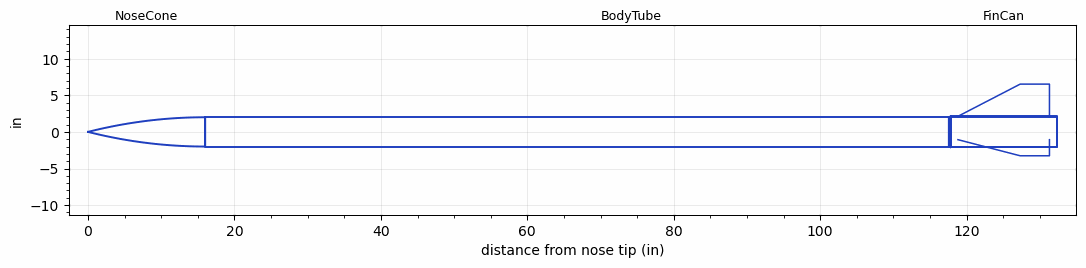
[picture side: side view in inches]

<RASAeroDocument>
 <FileVersion>2</FileVersion>
 <RocketDesign>
  <NoseCone>
   <Length>16</Length>
   <Diameter>4</Diameter>
   <Shape>Tangent Ogive</Shape>
   <Location>0</Location>
  </NoseCone>
  <BodyTube>
   <Length>116.3125</Length>
   <Diameter>4</Diameter>
   <Location>16</Location>
  </BodyTube>
  <FinCan>
   <Length>14.5</Length>
   <Diameter>4.25</Diameter>
   <InsideDiameter>4</InsideDiameter>
   <Location>132.3125</Location>
   <ShoulderLength>0.2415</ShoulderLength>
   <Offset>-14.5</Offset>
   <Fin>
    <Count>3</Count>
    <Chord>12.5</Chord>
    <Span>4.4</Span>
    <SweepDistance>8.5</SweepDistance>
    <TipChord>4</TipChord>
    <Thickness>0.125</Thickness>
    <Location>13.5</Location>
    <AirfoilSection>Hexagonal</AirfoilSection>
    <FX1>0.25</FX1>
    <FX3>0.125</FX3>
   </Fin>
  </FinCan>
  <Surface>Smooth (Zero Roughness)</Surface>
  <ModifiedBarrowman>False</ModifiedBarrowman>
  <Turbulence>False</Turbulence>
  <SustainerNozzle>2.5</SustainerNozzle>
  <UseBooster1>False</UseBooster1>
  <UseBooster2>False</UseBooster2>
  <Comments>Full Metal Jacket - BALLS 005
O10000 Motor
Frank Kosdon
Black Rock Launch Site

Optical Track
Altitude = 37981 ft

RASAero II Prediction = 38772 ft
Error = 2.08%
</Comments>
 </RocketDesign>
 <LaunchSite>
  <Altitude>3933</Altitude>
  <Pressure>0</Pressure>
  <RodAngle>0</RodAngle>
  <RodLength>12</RodLength>
  <Temperature>80</Temperature>
  <WindSpeed>0</WindSpeed>
 </LaunchSite>
 <Recovery>
  <Altitude1>1000</Altitude1>
  <Altitude2>1000</Altitude2>
  <DeviceType1>Parachute</DeviceType1>
  <DeviceType2>None</DeviceType2>
  <Event1>False</Event1>
  <Event2>False</Event2>
  <Size1>36</Size1>
  <Size2>1</Size2>
  <EventType1>Apogee</EventType1>
  <EventType2>None</EventType2>
  <CD1>1.33</CD1>
  <CD2>1.33</CD2>
 </Recovery>
 <SimulationList>
  <Simulation>
   <SustainerEngine>O10000  (Hist)</SustainerEngine>
   <SustainerLaunchWt>70</SustainerLaunchWt>
   <SustainerNozzleDiameter>2.5</SustainerNozzleDiameter>
   <SustainerCG>86</SustainerCG>
   <SustainerIgnitionDelay>0</SustainerIgnitionDelay>
   <Booster1SeparationDelay>0</Booster1SeparationDelay>
   <Booster1IgnitionDelay>0</Booster1IgnitionDelay>
   <IncludeBooster1>False</IncludeBooster1>
   <Booster2Delay>0</Booster2Delay>
   <IncludeBooster2>False</IncludeBooster2>
   <TimetoApogee>45.08844</TimetoApogee>
   <MaxAltitude>38771.61</MaxAltitude>
   <MaxVelocity>2566.523</MaxVelocity>
  </Simulation>
 </SimulationList>
</RASAeroDocument>
